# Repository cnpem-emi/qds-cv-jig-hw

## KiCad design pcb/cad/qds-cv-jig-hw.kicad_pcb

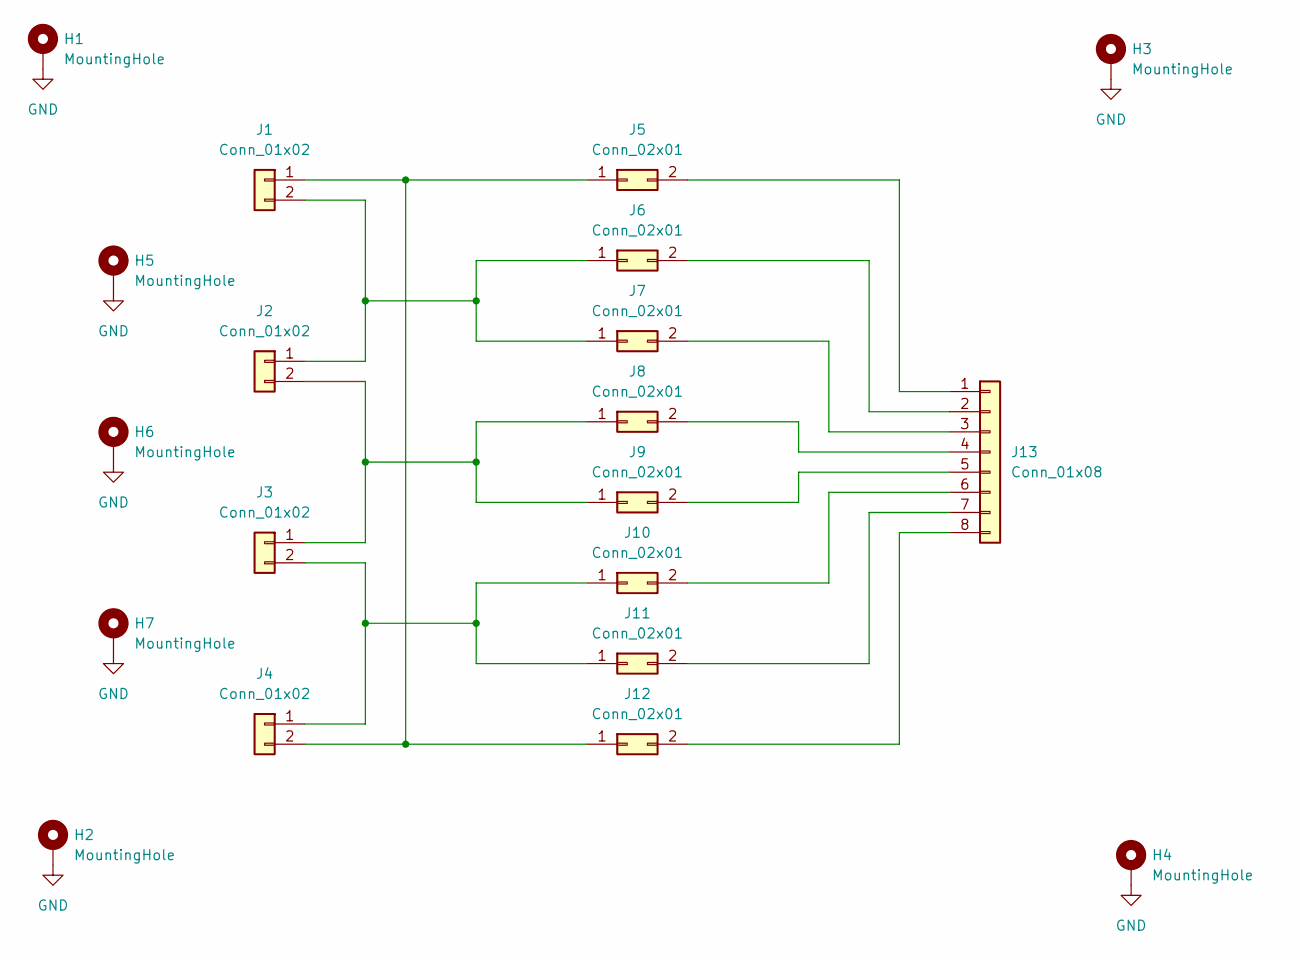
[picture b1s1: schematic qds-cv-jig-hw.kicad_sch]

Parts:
H1, H2, H3, H4: MountingHole; MountingHole_3.2mm_M3_Pad
H5, H6, H7: MountingHole; Potentiometer_Vishay_534
J1, J2, J3, J4: Conn_01x02; PhoenixContact_MSTBVA_2,5_2-G-5,08_1x02_P5.08mm_Vertical
J5, J6, J7, J8, J9, J10, J11, J12: Conn_02x01; PinHeader_2x01_P2.54mm_Vertical
J13: Conn_01x08; PhoenixContact_MSTBVA_2,5_8-G-5,08_1x08_P5.08mm_Vertical

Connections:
GND: H1.1, H2.1, H3.1, H4.1, H5.1, H6.1, H7.1
unnamed: J1.1, J4.2, J5.1, J12.1
unnamed: J1.2, J2.1, J6.1, J7.1
unnamed: J2.2, J3.1, J8.1, J9.1
unnamed: J3.2, J4.1, J10.1, J11.1
unnamed: J10.2, J13.6
unnamed: J11.2, J13.7
unnamed: J12.2, J13.8
unnamed: J5.2, J13.1
unnamed: J6.2, J13.2
unnamed: J7.2, J13.3
unnamed: J8.2, J13.4
unnamed: J9.2, J13.5

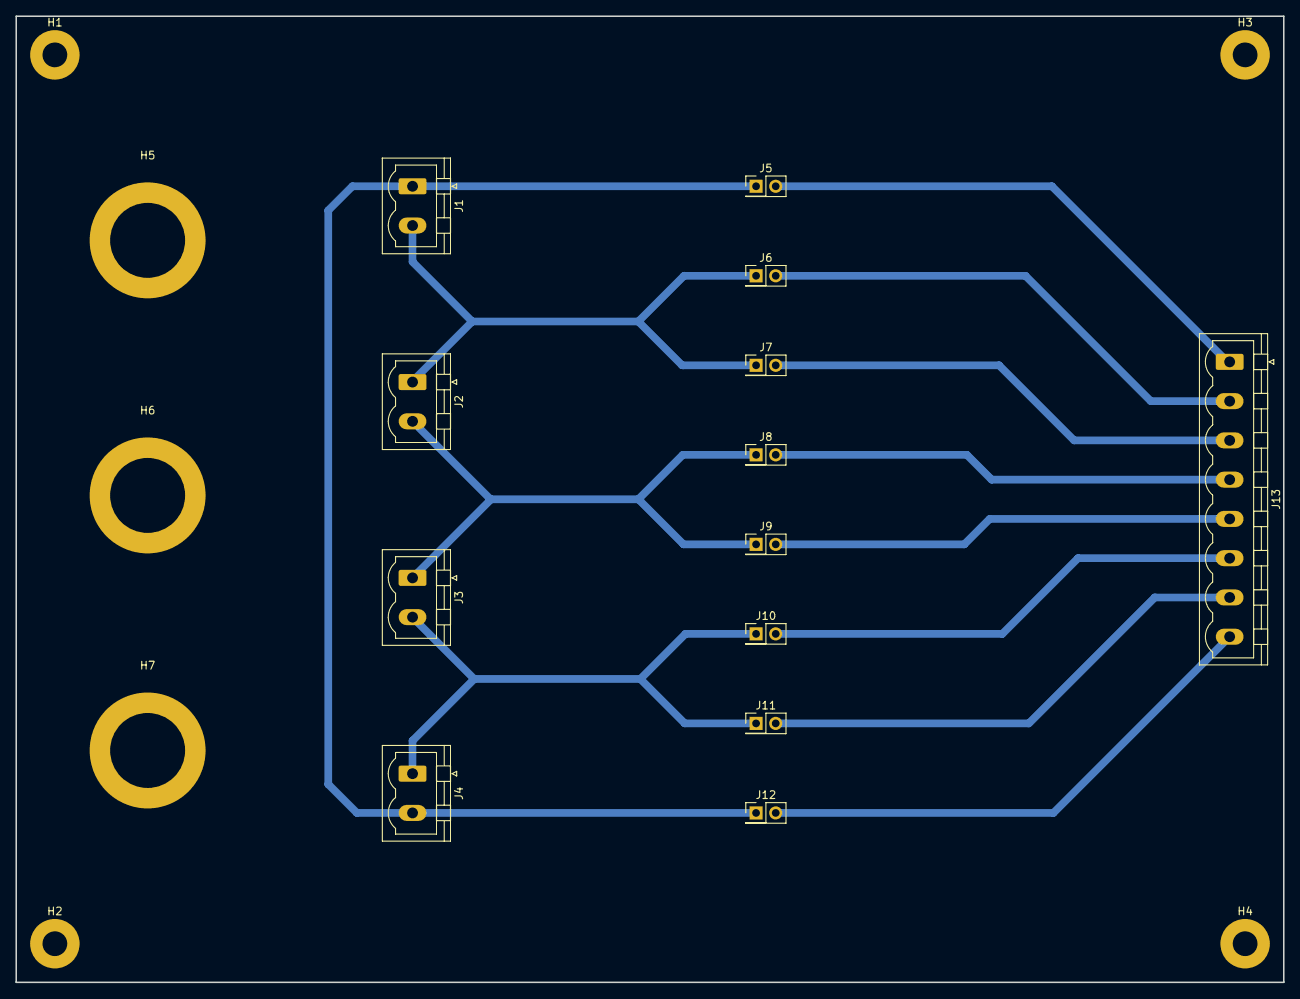
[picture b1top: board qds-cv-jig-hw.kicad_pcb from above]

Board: 2 copper layers, 164.0 x 125.0 mm, 20 parts (0 on the bottom side), 13 nets.

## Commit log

2023-08-08 Include connectors, jumpers, tracks and mounting holes on schematics and PCB
2023-08-08 Include board outline, potentiometer and spacers, place GND fill
2023-08-08 Remove tracks residues
2023-08-08 Generate gerber files
2023-08-08 Regenerate gerber files
